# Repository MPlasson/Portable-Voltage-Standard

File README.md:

# Portable Voltage Standard
A portable voltage reference module, based on the REF7050 chip from Ti.

## Features

- Stable 5V output with high accuracy (< 0.025%)
- Very low temperature coefficient (< 2ppm/°C)
- Battery powered for lowest noise & portability
- Power Good LED indicator
- Low Battery LED indicator

## Tests status

Link to test report: [TestReport](tests/index.md)

- [x] Initial bringup
- [ ] Line regulation
- [ ] Load regulation
- [x] Current consumption
- [ ] Low battery LED trigger voltage
- [x] Ambient temperature accuracy
- [x] Temperature drift [20°C - 50°C]
- [ ] Output stability (100h minimum)

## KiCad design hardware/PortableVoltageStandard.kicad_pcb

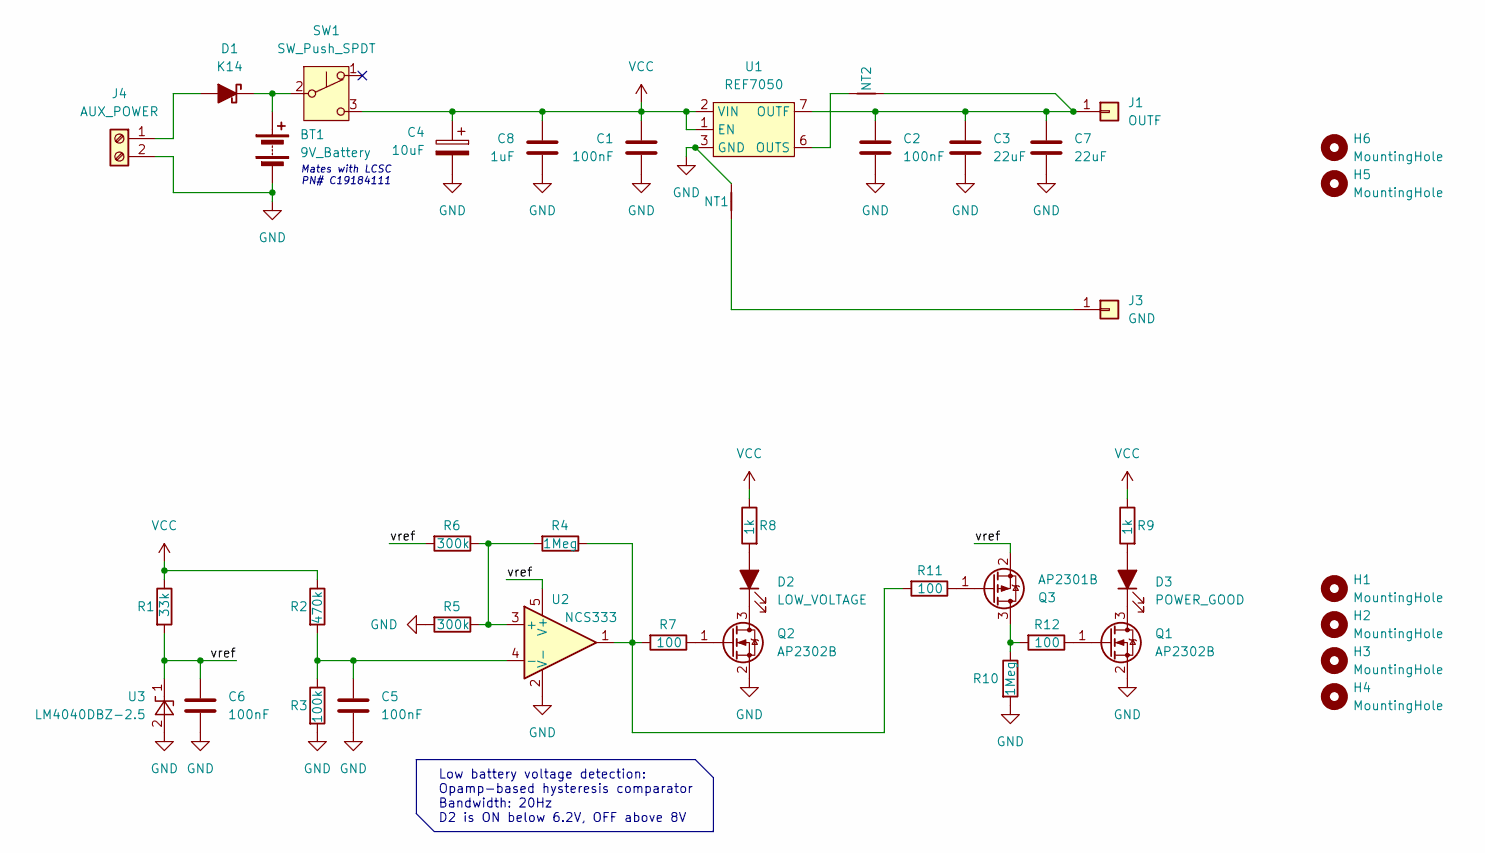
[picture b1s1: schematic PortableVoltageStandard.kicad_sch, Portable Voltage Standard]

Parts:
BT1: 9V_Battery; JST_EH_B2B-EH-A_1x02_P2.50mm_Vertical; LCSC C3018737
C1, C2, C5, C6: 100nF; C_0603_1608Metric; LCSC C14663
C3, C7: 22uF; C_0805_2012Metric; LCSC C602037
C4: 10uF; CP_Elec_5x5.3; LCSC C365682
C8: 1uF; C_0805_2012Metric; LCSC C28323
D1: K14; D_SOD-123F; LCSC C908662
D2: LOW_VOLTAGE; LED_D5.0mm; LCSC C7470717
D3: POWER_GOOD; LED_D5.0mm; LCSC C7433083
H1, H2, H3, H4, H5, H6: MountingHole; MountingHole_3.2mm_M3
J1: OUTF; banana_socket_24.245.1_Amass_rouge; LCSC C7437326
J3: GND; banana_socket_24.245.2_Amass_noire; LCSC C7437327
J4: AUX_POWER; TerminalBlock_MetzConnect_Type171_RT13702HBWC_1x02_P7.50mm_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
NT1, NT2: NetTie_2; NetTie-2_SMD_Pad0.5mm
Q1, Q2: AP2302B; SOT-23; LCSC C406812
Q3: AP2301B; SOT-23; LCSC C2763847
R1: 33k; R_0603_1608Metric; LCSC C126359
R2: 470k; R_0603_1608Metric; LCSC C114622
R3: 100k; R_0603_1608Metric; LCSC C14675
R4, R10: 1Meg; R_0603_1608Metric; LCSC C105578
R5, R6: 300k; R_0603_1608Metric; LCSC C114667
R7, R11, R12: 100; R_0603_1608Metric; LCSC C105588
R8, R9: 1k; R_0603_1608Metric; LCSC C22548
SW1: SW_Push_SPDT; SPEF210200; LCSC C278409
U1: REF7050; Analog_LCC-8_5x5mm_P1.27mm; LCSC C6760318
U2: NCS333; SOT-23-5; LCSC C74336
U3: LM4040DBZ-2.5; SOT-23; LCSC C2156989

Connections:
/vref: C6.1, Q3.2 (S), R1.2, R6.2, U2.5 (V+), U3.1 (K)
GND: BT1.2 (-), C1.2, C2.2, C3.2, C4.2, C5.2, C6.2, C7.2, C8.2, J4.2, NT1.2, Q1.2 (S), Q2.2 (S), R3.2, R5.2, R10.2, U1.3 (GND), U1.4 (GND), U1.5 (GND), U1.8 (GND), U2.2 (V-), U3.2 (A)
unnamed: BT1.1 (+), D1.1 (K), SW1.2 (B)
unnamed: D1.2 (A), J4.1
unnamed: D2.2 (A), R8.2
unnamed: D2.1 (K), Q2.3 (D)
unnamed: D3.2 (A), R9.2
unnamed: D3.1 (K), Q1.3 (D)
unnamed: C2.1, C3.1, C7.1, J1.1, NT2.2, U1.7 (OUTF)
unnamed: J3.1, NT1.1
unnamed: Q1.1 (G), R12.1
unnamed: Q2.1 (G), R7.1
unnamed: Q3.3 (D), R10.1, R12.2
unnamed: Q3.1 (G), R11.1
unnamed: R4.1, R7.2, R11.2, U2.1
unnamed: NT2.1, U1.6 (OUTS)
unnamed: R4.2, R5.1, R6.1, U2.3 (+)
unnamed: C5.1, R2.2, R3.1, U2.4 (-)
VCC: C1.1, C4.1, C8.1, R1.1, R2.1, R8.1, R9.1, SW1.3 (C), U1.1 (EN), U1.2 (VIN)

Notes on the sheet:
Low battery voltage detection: Opamp-based hysteresis comparator Bandwidth: 20Hz D2 is ON below 6.2V, OFF above 8V
Mates with LCSC PN# C19184111

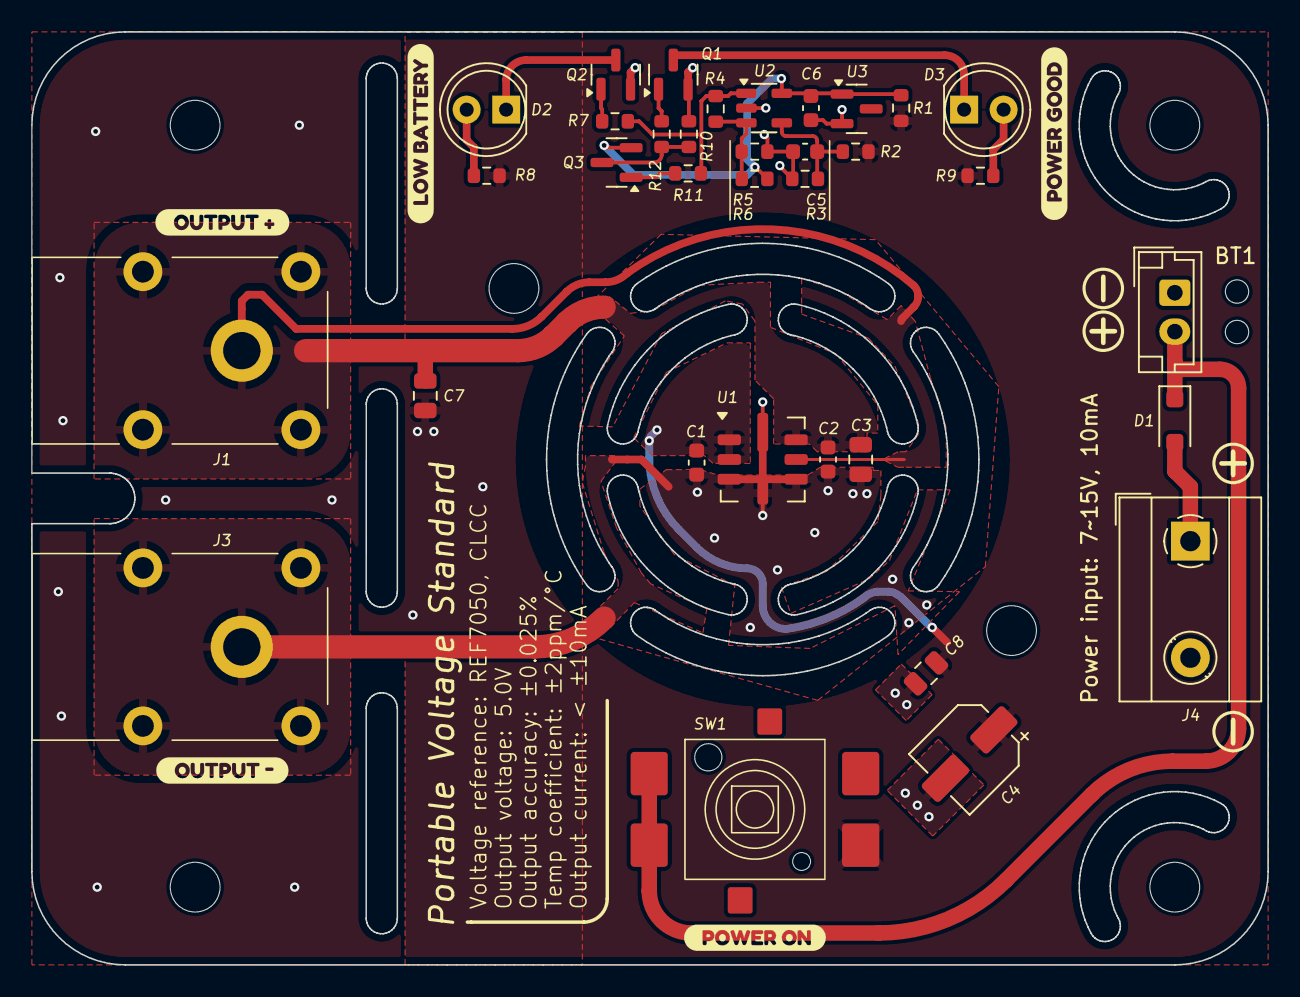
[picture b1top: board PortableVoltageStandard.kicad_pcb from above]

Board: 2 copper layers, 79.5 x 60.0 mm, 49 parts (0 on the bottom side), 19 nets.

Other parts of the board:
H3#2, H3#3: MountingHole; MountingHole_3.2mm_M3
kibuzzard-678D0B69: G***; kibuzzard-678D0B69
kibuzzard-678D07AC: G***; kibuzzard-678D07AC
kibuzzard-678D073D: G***; kibuzzard-678D073D
kibuzzard-678D0758: G***; kibuzzard-678D0758
kibuzzard-678D0795: G***; kibuzzard-678D0795

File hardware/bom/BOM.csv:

"Reference","Value","Datasheet","Footprint","Qty","DNP","LCSC"
"BT1","9V_Battery","~","Connector_JST:JST_EH_B2B-EH-A_1x02_P2.50mm_Vertical","1","","C3018737"
"C1,C2,C5,C6","100nF","~","Capacitor_SMD:C_0603_1608Metric","4","","C14663"
"C3,C7","22uF","~","Capacitor_SMD:C_0805_2012Metric","2","","C602037"
"C4","10uF","~","Capacitor_SMD:CP_Elec_5x5.3","1","","C365682"
"C8","1uF","~","Capacitor_SMD:C_0805_2012Metric","1","","C28323"
"D1","K14","~","Diode_SMD:D_SOD-123F","1","","C908662"
"D2","LOW_VOLTAGE","~","LED_THT:LED_D5.0mm","1","","C7470717"
"D3","POWER_GOOD","~","LED_THT:LED_D5.0mm","1","","C7433083"
"J1","OUTF","~","KICAD_GENERAL_LIBRARY:banana_socket_24.245.1_Amass_rouge","1","","C7437326"
"J3","GND","~","KICAD_GENERAL_LIBRARY:banana_socket_24.245.2_Amass_noire","1","","C7437327"
"J4","AUX_POWER","~","TerminalBlock_MetzConnect:TerminalBlock_MetzConnect_Type171_RT13702HBWC_1x02_P7.50mm_Horizontal","1","",""
"Q1,Q2","AP2302B","https://www.lcsc.com/datasheet/lcsc_datasheet_2411201841_ALL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","Package_TO_SOT_SMD:SOT-23","2","","C406812"
"Q3","AP2301B","https://www.lcsc.com/datasheet/lcsc_datasheet_2411201843_ALL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","Package_TO_SOT_SMD:SOT-23","1","","C2763847"
"R1","33k","~","Resistor_SMD:R_0603_1608Metric","1","","C126359"
"R2","470k","~","Resistor_SMD:R_0603_1608Metric","1","","C114622"
"R3","100k","~","Resistor_SMD:R_0603_1608Metric","1","","C14675"
"R4,R10","1Meg","~","Resistor_SMD:R_0603_1608Metric","2","","C105578"
"R5,R6","300k","~","Resistor_SMD:R_0603_1608Metric","2","","C114667"
"R7,R11,R12","100","~","Resistor_SMD:R_0603_1608Metric","3","","C105588"
"R8,R9","1k","~","Resistor_SMD:R_0603_1608Metric","2","","C22548"
"SW1","SW_Push_SPDT","~","KICAD_GENERAL_LIBRARY:SPEF210200","1","","C278409"
"U1","REF7050","https://www.lcsc.com/datasheet/lcsc_datasheet_2309251242_Tex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","Package_LCC:Analog_LCC-8_5x5mm_P1.27mm","1","","C6760318"
"U2","NCS333","https://www.onsemi.com/pdf/datasheet/ncs333-d.pdf","Package_TO_SOT_SMD:SOT-23-5","1","","C74336"
"U3","LM4040DBZ-2.5","http://www.ti.com/lit/ds/symlink/lm4040-n.pdf","Package_TO_SOT_SMD:SOT-23","1","","C2156989"

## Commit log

2025-01-19 Added zip file for gerbers
2025-01-19 Renamed image files
2025-01-19 HW finishing & mechanical beginning
    Final modifications to the hardware side:
    - BOM updated
    - LCSC PN added to sch/bom
    Initial work on mechanical enclosure:
    - Bottom & top case started
    - Power button added
2025-01-19 Added mechanical step files
    Added large STEP files
2025-01-19 Updated folder names to be more explicit
2025-01-21 Front panel work
    Initial work on front panel design (kicad project creation)
    Added more sub folders to /electronics
    Encosure: changed the push button knob to a diameter of 18mm for ease of use
2025-01-22 Mech update
    Created front panel bezel
    Added screws to assembly
    Updated the screw length for more grip
2025-01-23 Update to the enclosure
    Modified screw type: M3 machine screws, with metal threaded inserts
2025-01-23 Front panel improvement
    Began working on the front panel design
    Added to mech assembly
2025-01-25 Electronics simulation files added
2025-02-09 Enclosure changes
    Added lips to all mating parts
    New design for power button: soft press fit into the pushbutton
2025-02-09 STL export for first 3D print
2025-03-03 Enclosure update
    Rotated the9V battery to a a thinner enclosure & be able to cable manage the inside
    Fixed misalignment between banana jacks & enclosure
2025-03-03 Updated tests results
2025-03-03 Renamed testResults.md
